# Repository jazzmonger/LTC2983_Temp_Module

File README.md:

# LTC2983 Temperature Module

ESPHome firmware and KiCad hardware designs for reading precision temperature sensors through the [Analog Devices LTC2983](https://www.analog.com/en/products/ltc2983.html) — a 20-channel multi-sensor ADC supporting RTDs, thermocouples, diodes, and thermistors.

This repo is a **standalone** ESPHome device that reads **5× PT1000 RTDs** and **5× K-type thermocouples** in one multi-channel conversion cycle, with per-channel fault sensors. The board and can be adapted to other sensor combinations on unused LTC2983 channels.

## Hardware

| Component | Description |
|-----------|-------------|
| **MCU** | ESP32-S3-DevKitC-1 class (16 MB flash, 8 MB octal PSRAM) |
| **Sensor IC** | LTC2983 |
| **Target layout** | Stacked 5 RTD + 5 TC topology ([DC2210A](schematics/dc2210a-5rtd-5tc-wiring.png) reference) |
| **Carrier PCB** | Custom [DC2209A1](KiCad/DC2209A1.kicad_sch) KiCad design — LTC2983 breakout with screw terminals and SPI header |

### SPI wiring (ESP32-S3 → LTC2983)

| Signal | GPIO |
|--------|------|
| CS     | 2    |
| CLK    | 9    |
| MOSI   | 5    |
| MISO   | 4    |

### Channel map

| Sensor | LTC2983 CH | Type | Notes |
|--------|------------|------|-------|
| RTD 1 | 4 | PT1000, 2-wire | Sense pair CH4 ↔ CH3 (COM) |
| RTD 2 | 6 | PT1000, 2-wire | CH6 ↔ CH5 (COM) |
| RTD 3 | 8 | PT1000, 2-wire | CH8 ↔ CH7 (COM) |
| RTD 4 | 10 | PT1000, 2-wire | CH10 ↔ CH9 (COM) |
| RTD 5 | 12 | PT1000, 2-wire | CH12 ↔ CH11 (COM) |
| TC 1 | 13 | K-type, single-ended | TC− → COM; CJC via CH20 diode |
| TC 2 | 14 | K-type | |
| TC 3 | 15 | K-type | |
| TC 4 | 16 | K-type | |
| TC 5 | 17 | K-type | |

Shared excitation: **CH2** = 2 kΩ sense resistor (RSENSE hub). Odd channels CH3/5/7/9/11 tie to CH2. Cold-junction compensation uses a **2N3906 diode on CH20** (emitter → CH20, base + collector → COM).

See `schematics/dc2210a-5rtd-5tc-wiring.png` and `schematics/dc2210a1-sch.pdf` for full wiring of demo circuit or KiCad schematics for this implementation.

## Firmware

The LTC2983 is driven by a custom C++ handler included directly in the ESPHome config — no external component package required.

| File | Purpose |
|------|---------|
| `LTC2983_Temp_Module.yaml` | ESPHome config — 10 template sensors, fault text sensors, 500 ms poll |
| `ltc2983_handler.h` | SPI init, channel assignment, multi-channel conversion, fault decode |
| `common/wifi.yaml` | WiFi / captive portal / web server |

Polling uses non-blocking `read_ltc2983_sensors()`: start a multi-channel conversion (~2 s), publish all channels when DONE, then start the next cycle.

### Home Assistant entities

**Temperature sensors**

- `RTD CH4` … `RTD CH12` — RTD 1–5 (°C)
- `TC 1` … `TC 5` — thermocouples (°C)

**Fault text sensors** (one per channel — `OK`, `Open Circuit`, `Overrange`, etc.)

- `Fault CH4`, `Fault CH6`, `Fault CH8`, `Fault CH10`, `Fault CH12`
- `Fault TC1` … `Fault TC5`

## Project layout

```
LTC2983_Temp_Module.yaml   # ESPHome config
ltc2983_handler.h          # LTC2983 SPI driver
common/wifi.yaml           # WiFi package
schematics/                # Wiring diagrams and reference schematics
KiCad/                     # DC2209A1 carrier board (sch, pcb, gerbers)
Demo Circuit Board/        # Analog Devices DC2209A reference files
LTC2983 sketch and info.c  # Reference channel-config notes
```

## Getting started

### Prerequisites

- [ESPHome](https://esphome.io/) installed
- ESP32-S3-DevKitC-1 connected via USB
- LTC2983 board wired per SPI table and channel map above

### Secrets

Create `secrets.yaml` in the project root (gitignored):

```yaml
wifi_ssid: "YourSSID"
wifi_password: "YourPassword"
```

### Build and flash

Copy to `/tmp` before running ESPHome (avoids path issues):

```bash
cp -r "./LTC2983_Temp_Module" /tmp/ltc2983-temp-module/
cd /tmp/ltc2983-temp-module
esphome run LTC2983_Temp_Module.yaml --device /dev/cu.usbserial-XXXX
```

Replace `/dev/cu.usbserial-XXXX` with your serial port. Logs stream automatically — do not use `--no-logs`.

### Home Assistant

Add the device through the ESPHome integration after flashing. All 10 temperature sensors and 10 fault sensors appear under the `ltc2983-temp-module` device.

## References

- [LTC2983 datasheet](https://www.analog.com/media/en/technical-documentation/data-sheets/ltc2983-2984.pdf)
- [DC2210A demo board](https://www.analog.com/en/resources/evaluation-hardware-and-software/evaluation-boards-kits/dc2210a.html) — 5 RTD + 5 TC reference
- [DC2296A evaluation kit](https://www.analog.com/en/resources/evaluation-hardware-and-software/evaluation-boards-kits/dc2296a.html)
- `schematics/dc2210a1-sch.pdf` — DC2210A schematic
- `schematics/dc2213a1-sch.pdf` — DC2213A schematic (single RTD demo)
- `KiCad/Gerbers/` — fabrication outputs for the DC2209A1 carrier board

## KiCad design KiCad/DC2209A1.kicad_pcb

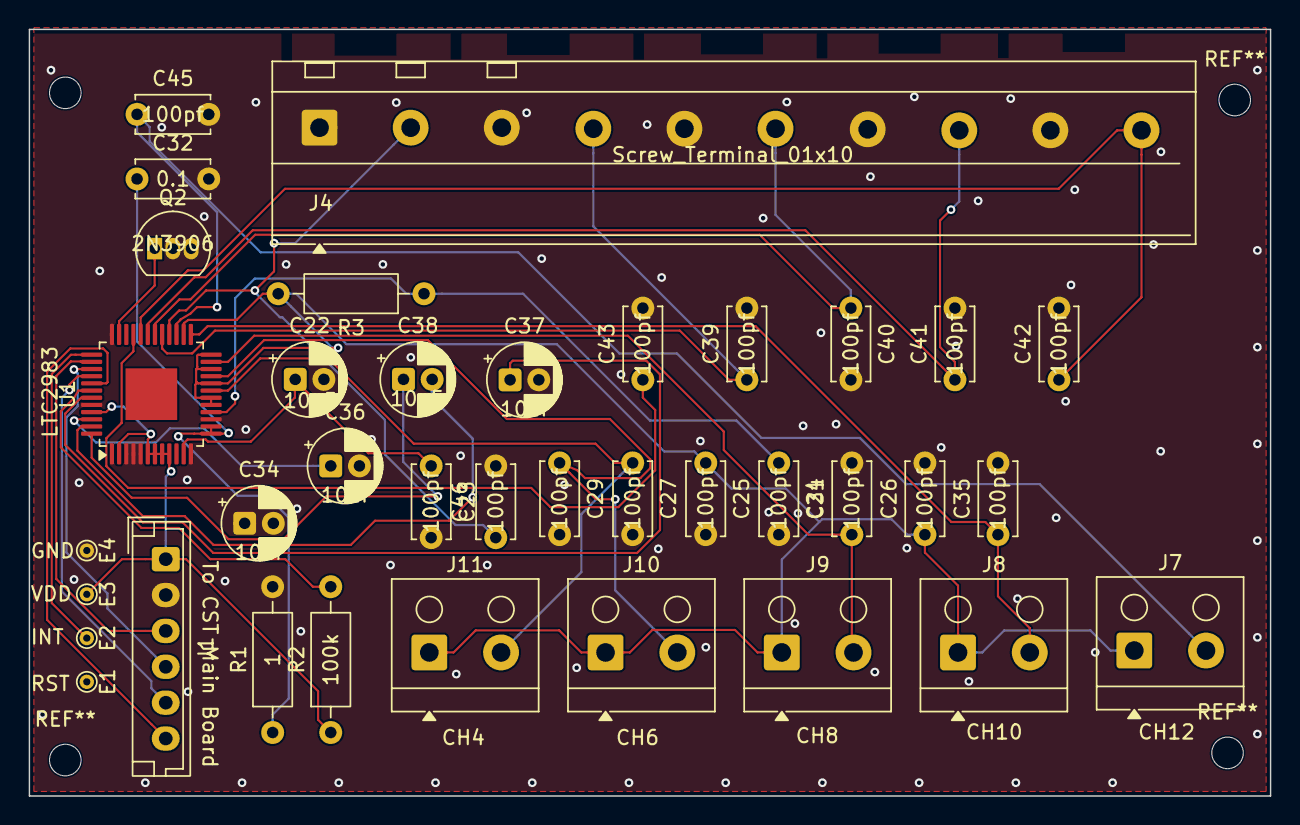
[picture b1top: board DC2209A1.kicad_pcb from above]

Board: 2 copper layers, 86.5 x 53.4 mm, 37 parts (0 on the bottom side), 28 nets.

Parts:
C22, C34, C36, C37, C38: 10uF; CP_Radial_D5.0mm_P2.00mm
C23, C24, C25, C26, C27, C29, C31, C35, C39, C40, C41, C42, C43, C45, C46: 100pf; C_Disc_D5.0mm_W2.5mm_P5.00mm
C32: 0.1; C_Disc_D5.0mm_W2.5mm_P5.00mm
E1, E2, E3, E4: TestPoint; TestPoint_THTPad_D1.0mm_Drill0.5mm
J1: JST_XH_01x06; JST_EH_B6B-EH-A_1x06_P2.50mm_Vertical
J4: Screw_Terminal_01x10; TerminalBlock_10x03_P6.35mm_M3_screws
J7: CH12; TerminalBlock_RND_205-00001_1x02_P5.00mm_Horizontal
J8: CH10; TerminalBlock_RND_205-00001_1x02_P5.00mm_Horizontal
J9: CH8; TerminalBlock_RND_205-00001_1x02_P5.00mm_Horizontal
J10: CH6; TerminalBlock_RND_205-00001_1x02_P5.00mm_Horizontal
J11: CH4; TerminalBlock_RND_205-00001_1x02_P5.00mm_Horizontal
Q2: 2N3906; TO-92_Inline
R1: 1; R_Axial_DIN0207_L6.3mm_D2.5mm_P10.16mm_Horizontal
R2: 100k; R_Axial_DIN0207_L6.3mm_D2.5mm_P10.16mm_Horizontal
R3: 2k; R_Axial_DIN0207_L6.3mm_D2.5mm_P10.16mm_Horizontal
U1: LTC2983; LQFP-48-1EP_7x7mm_P0.5mm_EP3.6x3.6mm

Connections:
/CH20: Q2.1 (E), U1.35 (CH20)
/INTERRUPT: E2.1 (1_1), U1.37 (INTERRUPT)
/LDO: C37.1, U1.43 (LDO)
/NCS: J1.6, U1.41 (NCS)
/Q1: C38.1, U1.48 (Q1)
/Q2: C38.2, U1.47 (Q2)
/Q3: C36.1, U1.46 (Q3)
/RESETN: R2.2, U1.42 (RESETN)
/SCK: J1.3, U1.38 (SCK)
/SDI: J1.5, U1.40 (SDI)
/SDO: J1.4, U1.39 (SDO)
/VREFOUT: C32.1, R1.1, U1.13 (VREFOUT), U1.14 (VREFP)
/VREF_BYP: C22.1, C23.1, U1.11 (VREF_BYP)
CH1: C24.1, R3.1, U1.16 (CH1)
CH2: C25.1, C26.1, J7.1, J8.1, J9.1, J10.1, J11.1, R3.2, U1.17 (CH2), U1.18 (CH3), U1.20 (CH5), U1.22 (CH7), U1.24 (CH9), U1.26 (CH11)
CH4: C27.1, J11.2, U1.19 (CH4)
CH6: C29.1, J10.2, U1.21 (CH6)
CH8: C31.1, J9.2, U1.23 (CH8)
CH10: C35.1, J8.2, U1.25 (CH10)
CH12: C45.1, J7.2, U1.27 (CH12)
CH13: C46.1, J4.2, U1.28 (CH13)
CH14: C39.1, J4.4, U1.29 (CH14)
CH15: C40.1, J4.6, U1.30 (CH15)
CH16: C41.1, J4.8, U1.31 (CH16)
CH17: C42.1, J4.10, U1.32 (CH17)
CH18: C43.1, U1.33 (CH18)
GND: C22.2, C23.2, C24.2, C25.2, C26.2, C27.2, C29.2, C31.2, C32.2, C34.1, C34.2, C35.2, C36.2, C37.2, C39.2, C40.2, C41.2, C42.2, C43.2, C45.2, C46.2, E4.1 (1_1), J1.2, J4.1, J4.3, J4.5, J4.7, J4.9, Q2.2 (B), Q2.3 (C), R1.2, U1.1 (GND), U1.3 (GND), U1.4 (GND), U1.5 (GND), U1.12 (GND), U1.15 (GND), U1.36 (COM), U1.44 (GND)
VDD: E3.1 (1_1), J1.1, R2.1, U1.2 (VDD), U1.6 (VDD), U1.7 (VDD), U1.8 (VDD), U1.9 (VDD), U1.45 (VDD)
